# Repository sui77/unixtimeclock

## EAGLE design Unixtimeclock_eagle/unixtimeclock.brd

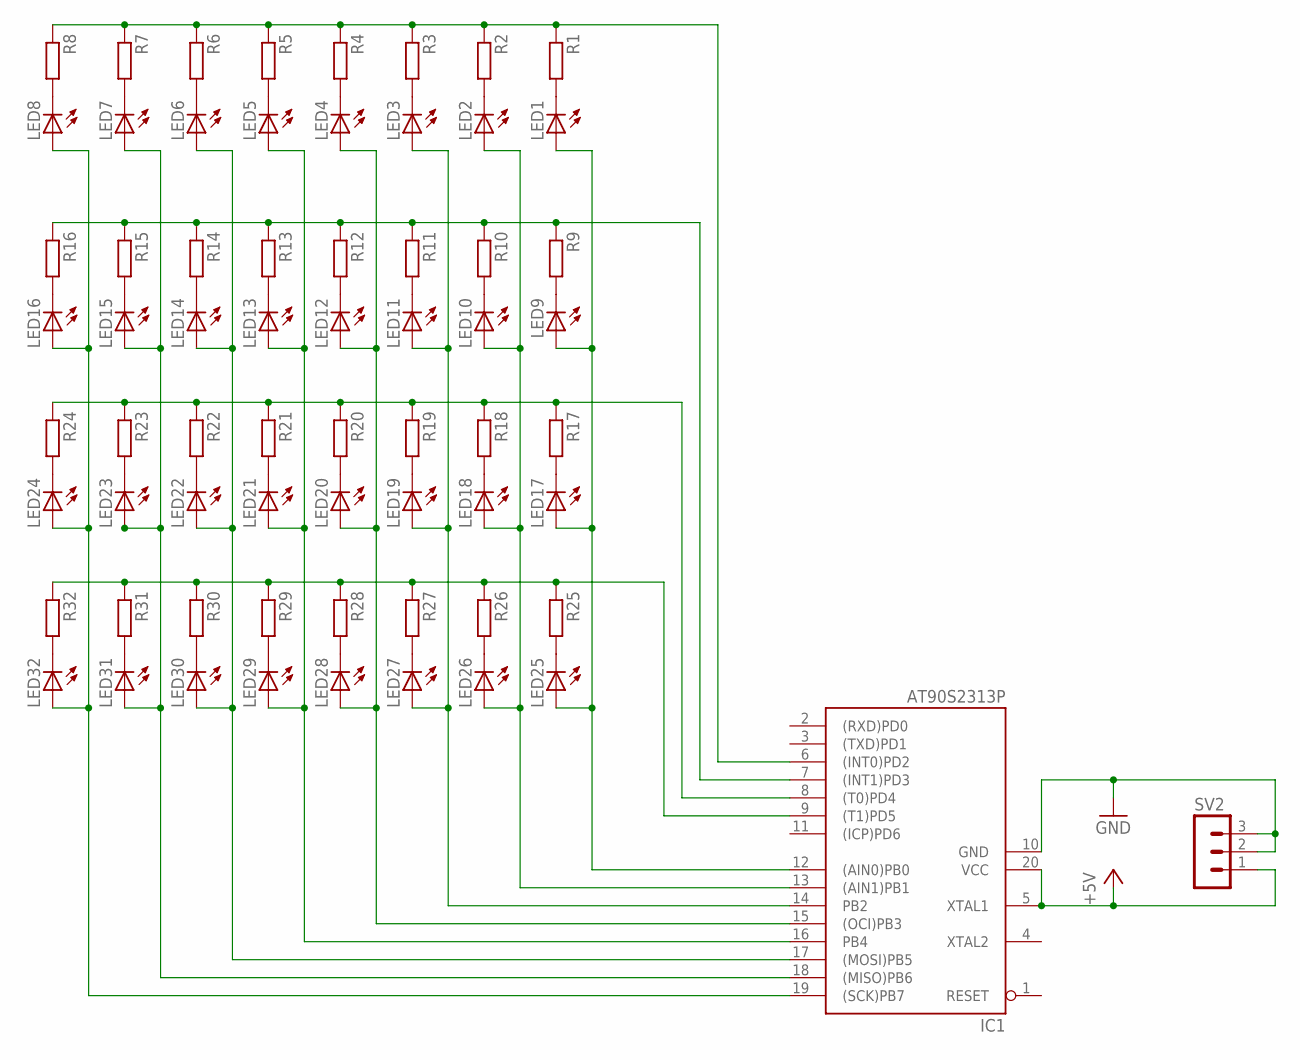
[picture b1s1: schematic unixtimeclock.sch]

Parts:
IC1: AT90S2313P; DIL20
LED1, LED2, LED3, LED4, LED5, LED6, LED7, LED8, LED9, LED10, LED11, LED12, LED13, LED14, LED15, LED16, LED17, LED18, LED19, LED20, LED21, LED22, LED23, LED24, LED25, LED26, LED27, LED28, LED29, LED30, LED31, LED32: LED5MM
R1, R2, R3, R4, R5, R6, R7, R8, R9, R10, R11, R12, R13, R14, R15, R16, R17, R18, R19, R20, R21, R22, R23, R24, R25, R26, R27, R28, R29, R30, R31, R32: R-EU_0207/10; 0207/10
SV2: MA03-1

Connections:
+5V: IC1.5 (XTAL1), IC1.20 (VCC), SV2.1
GND: IC1.10 (GND), SV2.2, SV2.3
unnamed: LED25.K (C), R25.2
unnamed: LED26.K (C), R26.2
unnamed: LED27.K (C), R27.2
unnamed: LED28.K (C), R28.2
unnamed: LED29.K (C), R29.2
unnamed: LED30.K (C), R30.2
unnamed: LED31.K (C), R31.2
unnamed: LED32.K (C), R32.2
unnamed: LED17.K (C), R17.2
unnamed: LED18.K (C), R18.2
unnamed: LED19.K (C), R19.2
unnamed: LED20.K (C), R20.2
unnamed: LED21.K (C), R21.2
unnamed: LED22.K (C), R22.2
unnamed: LED23.K (C), R23.2
unnamed: LED24.K (C), R24.2
unnamed: IC1.6 ((INT0)PD2), R1.1, R2.1, R3.1, R4.1, R5.1, R6.1, R7.1, R8.1
unnamed: LED9.K (C), R9.2
unnamed: LED10.K (C), R10.2
unnamed: LED11.K (C), R11.2
unnamed: LED12.K (C), R12.2
unnamed: LED13.K (C), R13.2
unnamed: LED14.K (C), R14.2
unnamed: LED15.K (C), R15.2
unnamed: LED16.K (C), R16.2
unnamed: LED1.K (C), R1.2
unnamed: LED2.K (C), R2.2
unnamed: LED3.K (C), R3.2
unnamed: LED4.K (C), R4.2
unnamed: LED5.K (C), R5.2
unnamed: LED6.K (C), R6.2
unnamed: LED7.K (C), R7.2
unnamed: LED8.K (C), R8.2
unnamed: IC1.7 ((INT1)PD3), R9.1, R10.1, R11.1, R12.1, R13.1, R14.1, R15.1, R16.1
unnamed: IC1.8 ((T0)PD4), R17.1, R18.1, R19.1, R20.1, R21.1, R22.1, R23.1, R24.1
unnamed: IC1.9 ((T1)PD5), R25.1, R26.1, R27.1, R28.1, R29.1, R30.1, R31.1, R32.1
unnamed: IC1.19 ((SCK)PB7), LED8.A, LED16.A, LED24.A, LED32.A
unnamed: IC1.17 ((MOSI)PB5), LED6.A, LED14.A, LED22.A, LED30.A
unnamed: IC1.16 (PB4), LED5.A, LED13.A, LED21.A, LED29.A
unnamed: IC1.15 ((OCI)PB3), LED4.A, LED12.A, LED20.A, LED28.A
unnamed: IC1.14 (PB2), LED3.A, LED11.A, LED19.A, LED27.A
unnamed: IC1.13 ((AIN1)PB1), LED2.A, LED10.A, LED18.A, LED26.A
unnamed: IC1.12 ((AIN0)PB0), LED1.A, LED9.A, LED17.A, LED25.A
unnamed: IC1.18 ((MISO)PB6), LED7.A, LED15.A, LED23.A, LED31.A

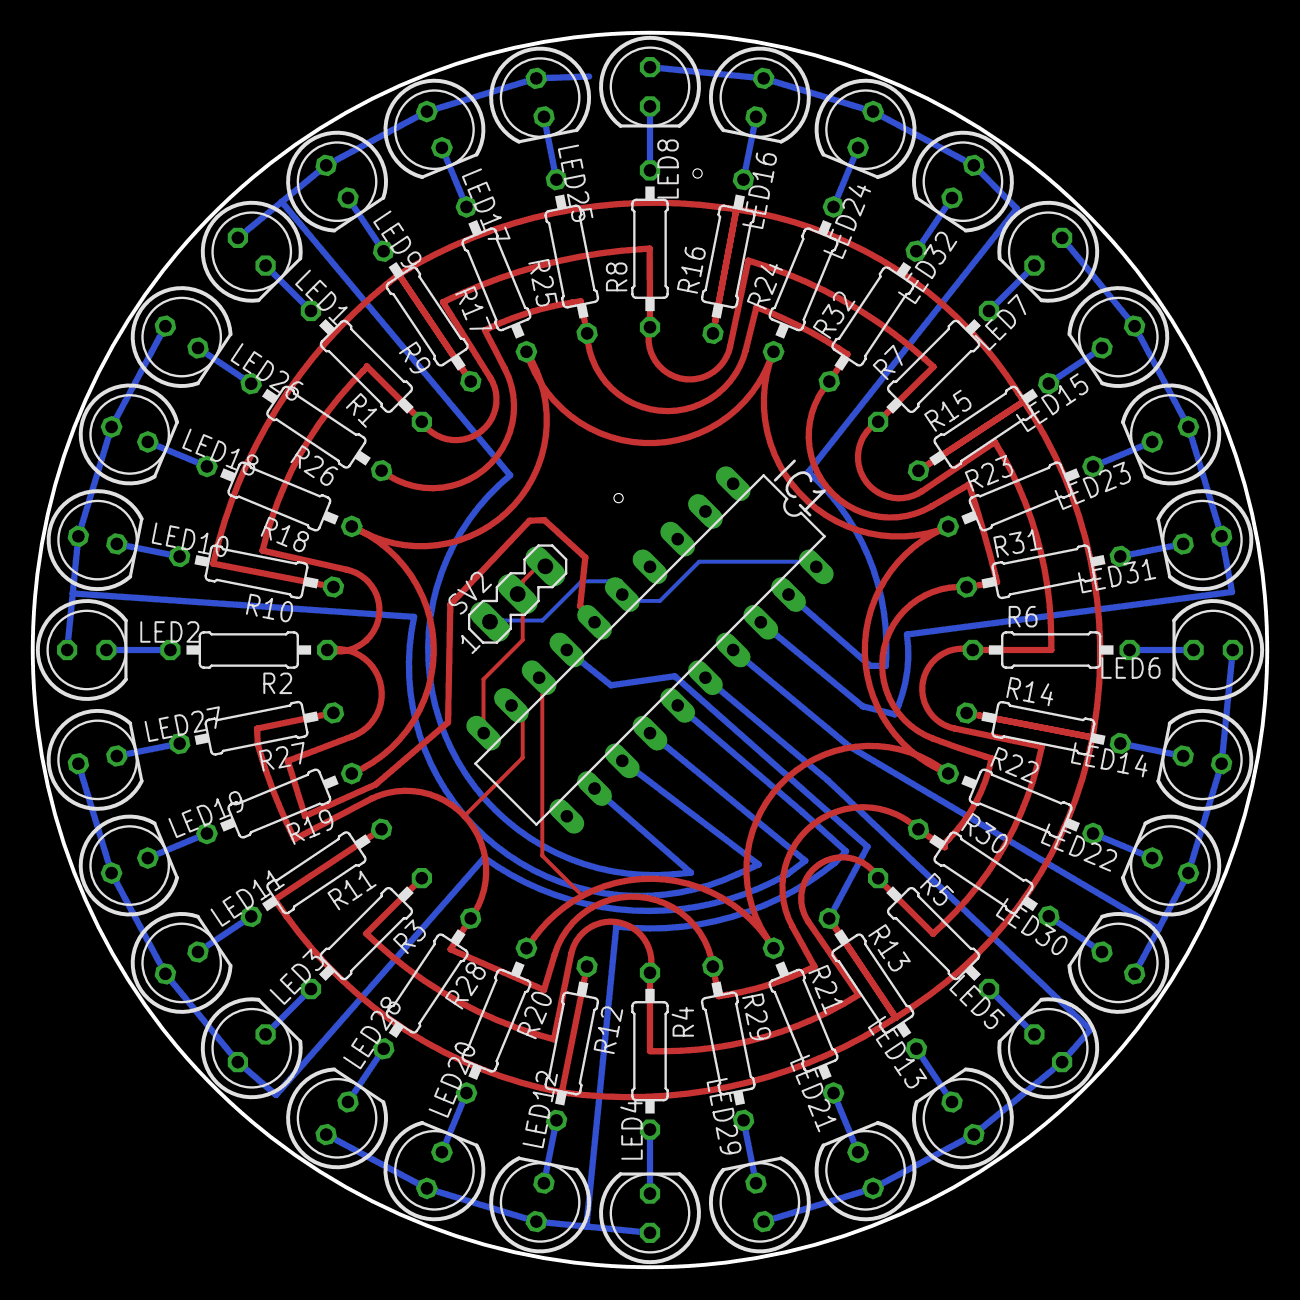
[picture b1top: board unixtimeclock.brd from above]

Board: 2 copper layers, 80.0 x 80.0 mm, 66 parts (0 on the bottom side), 46 nets.

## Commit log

2021-03-03 init
